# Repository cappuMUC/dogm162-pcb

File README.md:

# DOGM162x PCB

This is a KiCad project to create a universal PCB for a DOGM162 LCD by [Electronic Assembly](http://www.lcd-module.de/). It is connected over SPI and designed for a single color backlight.

It includes the PCB project and a 3D model of the display.

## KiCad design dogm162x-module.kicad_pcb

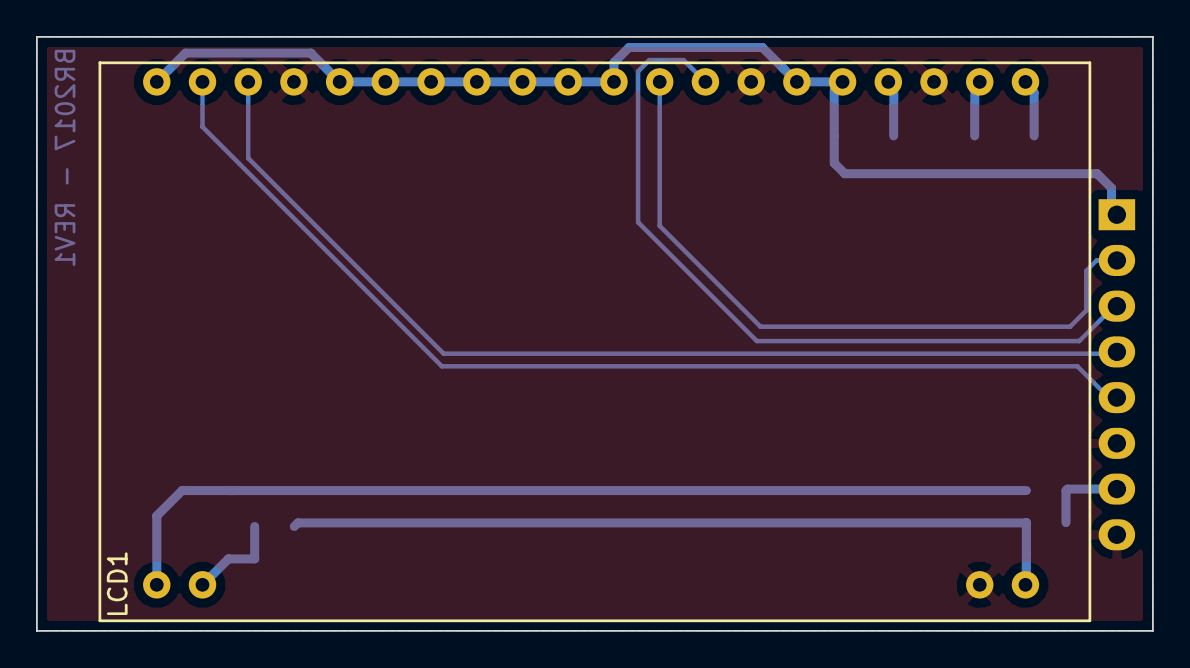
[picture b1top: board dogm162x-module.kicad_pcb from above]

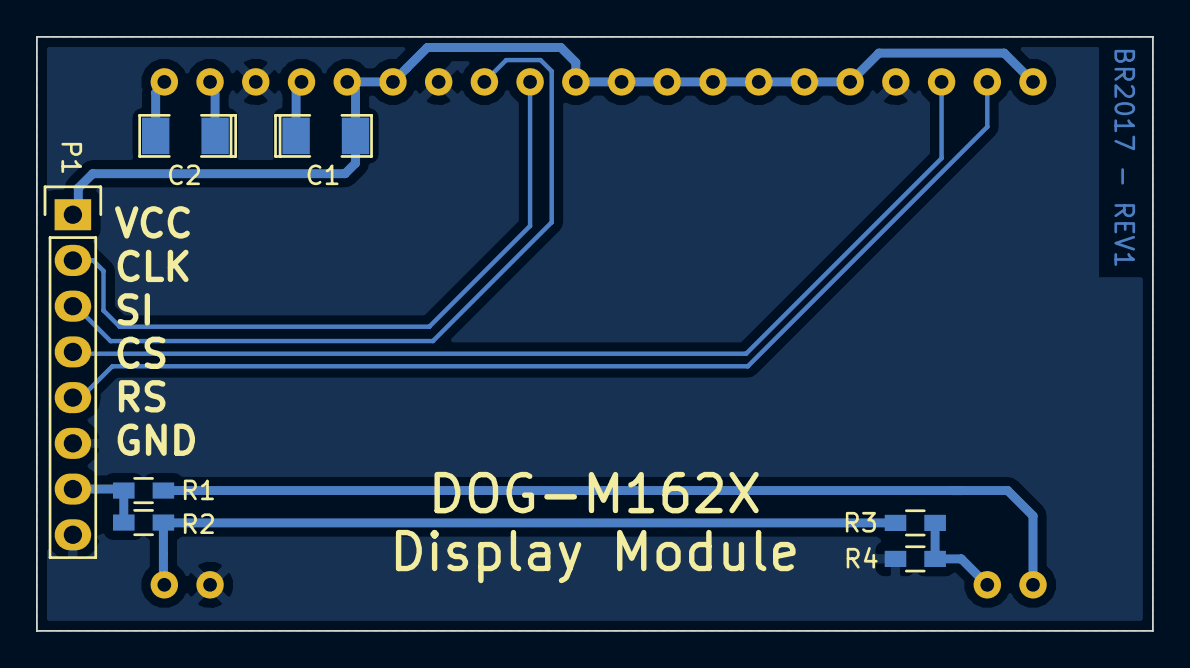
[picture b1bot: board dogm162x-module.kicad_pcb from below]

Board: 2 copper layers, 62.0 x 33.0 mm, 8 parts (7 on the bottom side), 13 nets.

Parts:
C1: 2,2uF; SMD-1206_Pol
C2: 1uF; SMD-1206_Pol
LCD1: DOGM162X
P1: CONN_01X08; Socket_Strip_Straight_1x08
R1, R2: 15R; R_0603_HandSoldering
R3, R4: 0R; R_0603_HandSoldering

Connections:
/A1: LCD1.1, R1.2
/A2: LCD1.20, R2.2, R3.1
/C1: LCD1.2, R3.2, R4.2
/CAP1N: C2.2, LCD1.21
/CAP1P: C2.1, LCD1.22
/CLK: LCD1.29, P1.2
/CS: LCD1.38, P1.4
/RS: LCD1.39, P1.5
/SI: LCD1.28, P1.3
/VCC_BACKLIGHT: P1.7, R1.1, R2.1
/VOUT: C1.1, LCD1.24
GND: LCD1.19, LCD1.23, LCD1.27, LCD1.37, P1.6, P1.8, R4.1
VCC: C1.2, LCD1.25, LCD1.26, LCD1.30, LCD1.31, LCD1.32, LCD1.33, LCD1.34, LCD1.35, LCD1.36, LCD1.40, P1.1

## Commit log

2016-04-28 added project files
2016-04-28 fixed missing components in schematic
2016-04-28 redesigned board
    added new outlines
    switched capacitors to smd types
    corrected position of the 3d display model
2016-04-29 beautification and minor changes
    resized board outlines
    changed 6 pin header to 8 pin header to get an extra pin for backlight
    power
    added silkscreen text
2017-01-20 dogm162 3d model path fixed
2017-01-20 removed missing library
2017-01-21 added images of the 3d model and moved schematic picture into the new folder 'pictures'
2017-01-21 added serial connection of LEDs and fixed 3d model path in parts
2017-01-22 increased revision number and fixed circuit at C1
    - increased revision number to Rev1 on schematic and pcb
    - an additional resistor is necessary to connect C1 to GND
2017-01-22 fixed LED circuit description
2017-01-23 added project description
2017-01-23 fixed formatting
2017-02-14 added picture of Rev0 to Readme
2017-02-14 added pin descriptions
